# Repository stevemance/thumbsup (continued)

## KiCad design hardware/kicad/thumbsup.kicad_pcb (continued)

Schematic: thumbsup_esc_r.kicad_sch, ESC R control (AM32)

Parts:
C300: 4.7u; C_0603_1608Metric; LCSC C19666
C301, C302, C304, C305, C306, C308: 100n; C_0402_1005Metric; LCSC C1525
C303: 1u; C_0402_1005Metric; LCSC C52923
C307: 10n; C_0402_1005Metric; LCSC C15195
C309: 10u 25V; C_0805_2012Metric; LCSC C15850
C310: 100n 50V; C_0603_1608Metric; LCSC C14663
J30: SWD; SWD_1x05_P1.27mm_Pads
R300, R303, R305, R306, R307, R311, R312, R313: 10k; R_0402_1005Metric; LCSC C25744
R301: 10k DNP; R_0402_1005Metric; LCSC C25744; not fitted
R302: 100k; R_0402_1005Metric; LCSC C25741
R304: 1k; R_0402_1005Metric; LCSC C11702
R308, R309, R310: 3.3k; R_0402_1005Metric; LCSC C25890
U30: AT32F421K8U7; QFN-32-1EP_5x5mm_P0.5mm_EP3.3x3.3mm; LCSC C2965611
U31: HX6288 / FD6288Q; QFN-24-1EP_4x4mm_P0.5mm_EP2.7x2.7mm; LCSC C54423134
U32: INA180A1; SOT-23-5; LCSC C122228

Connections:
+3V3_MCU: C300.1, C301.1, C302.1, C303.1, C304.1, C308.1, J30.1, U30.1 (VDD), U30.5 (VDDA), U30.17 (VDD2), U32.5 (V+); also elsewhere on the board
+VDRV: C309.1, C310.1, U31.4 (VCC); also elsewhere on the board
/ESC R control (AM32)/R_BEMF_A: R305.2, R308.1, R311.1, U30.6 (PA0_BEMFA)
/ESC R control (AM32)/R_BEMF_B: R306.2, R309.1, R312.1, U30.10 (PA4_BEMFB)
/ESC R control (AM32)/R_BEMF_C: R307.2, R310.1, R313.1, U30.11 (PA5_BEMFC)
/ESC R control (AM32)/R_HIN1: U30.20 (PA10_AH), U31.22 (HIN1)
/ESC R control (AM32)/R_HIN2: U30.19 (PA9_BH), U31.23 (HIN2)
/ESC R control (AM32)/R_HIN3: U30.18 (PA8_CH), U31.24 (HIN3)
/ESC R control (AM32)/R_ISENSE: C307.1, R304.2, U30.9 (PA3_I)
/ESC R control (AM32)/R_LIN1: U30.15 (PB1_AL), U31.1 (LIN1)
/ESC R control (AM32)/R_LIN2: U30.14 (PB0_BL), U31.2 (LIN2)
/ESC R control (AM32)/R_LIN3: U30.13 (PA7_CL), U31.3 (LIN3)
/ESC R control (AM32)/R_NRST: C305.1, J30.4, U30.4 (NRST)
/ESC R control (AM32)/R_SWCLK: J30.3, U30.24 (PA14_SWCLK)
/ESC R control (AM32)/R_SWDIO: J30.2, U30.23 (PA13_SWDIO)
/ESC R control (AM32)/R_VN: R311.2, R312.2, R313.2, U30.7 (PA1_VN)
/ESC R control (AM32)/R_VSENSE: C306.1, R302.2, R303.1, U30.12 (PA6_V)
DSHOT_R: R301.1, U30.27 (PB4_DSHOT); also elsewhere on the board
GND: C300.2, C301.2, C302.2, C303.2, C304.2, C305.2, C306.2, C307.2, C308.2, C309.2, C310.2, J30.5, R300.2, R301.2, R303.2, R308.2, R309.2, R310.2, U30.33 (EP_VSS), U31.6 (COM), U31.25 (EP), U32.2 (GND); also elsewhere on the board
I_R_S+: U32.3 (+); also elsewhere on the board
I_R_S-: U32.4 (-); also elsewhere on the board
MOTOR_R_A: R305.1, U31.18 (VS1); also elsewhere on the board
MOTOR_R_B: R306.1, U31.15 (VS2); also elsewhere on the board
MOTOR_R_C: R307.1, U31.12 (VS3); also elsewhere on the board
unnamed: R304.1, U32.1
unnamed: R300.1, U30.31 (BOOT0)
R_HO1: U31.19 (HO1); also elsewhere on the board
R_HO2: U31.16 (HO2); also elsewhere on the board
R_HO3: U31.13 (HO3); also elsewhere on the board
R_LO1: U31.11 (LO1); also elsewhere on the board
R_LO2: U31.10 (LO2); also elsewhere on the board
R_LO3: U31.9 (LO3); also elsewhere on the board
R_VB1: U31.20 (VB1); also elsewhere on the board
R_VB2: U31.17 (VB2); also elsewhere on the board
R_VB3: U31.14 (VB3); also elsewhere on the board
VBAT: R302.1; also elsewhere on the board

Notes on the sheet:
ESC R: AM32 cell — AT32F421 (target AT32DEV_F421) + FD6288Q gate driver + sense networks. Power stage on sheet esc_r_bridge.
Stock-hex scaling: voltage divider 100k/10k (TARGET_VOLTAGE_DIVIDER 110), current 1 mΩ × INA180A1 (20 V/V) = 20 mV/A (MILLIVOLT_PER_AMP 20).
HO/LO/VS/VB → bridge sheet
SWD (first bootloader flash)
1: +3V3 2: SWDIO 3: SWCLK 4: NRST 5: GND
DShot pull-down — DNP (AT32 idles high for AM32 1-wire)
Pack voltage → PA6 (11:1)
Cell current: 1 mΩ shunt → INA180A1 (20 V/V) → RC → PA3
BEMF dividers 10k/3.3k (4:1) and 10k virtual-neutral star → comparator
Decoupling — at U pins (C300…: AT32 VDD/VDDA, INA180, FD6288 VCC)

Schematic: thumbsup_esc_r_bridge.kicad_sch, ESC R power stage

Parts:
C320, C321, C322: 100n 50V; C_0603_1608Metric; LCSC C14663
C323, C324: 10u 50V; C_1206_3216Metric; LCSC C13585
C325: 470u 25V hybrid; CP_Elec_10x10.5; LCSC C242138
D30, D31, D32: 1N5819WS; D_SOD-323; LCSC C191023
J31: MOTOR R; MotorHoles_1x03_P5.90mm
NT30, NT31: Kelvin; NetTie-2_Kelvin_0.4mm
Q30, Q31, Q32, Q33, Q34, Q35: HYG015N04LS1C2; PQFN-8-EP_6x5mm_P1.27mm_Generic; LCSC C2874970
R320, R321, R322, R323, R324, R325: 10; R_0402_1005Metric; LCSC C25077
R326, R327, R328, R329, R330, R331: 10k; R_0402_1005Metric; LCSC C25744
R332, R333, R334: 2.2; R_0603_1608Metric; LCSC C22939
R335: 1mΩ 3W; R_2512_Shunt_Kelvin; LCSC C46961745

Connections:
+VDRV: R332.1, R333.1, R334.1; also elsewhere on the board
/ESC R power stage/I_R+: NT30.1, Q31.1 (S), Q31.2 (S), Q31.3 (S), Q33.1 (S), Q33.2 (S), Q33.3 (S), Q35.1 (S), Q35.2 (S), Q35.3 (S), R327.2, R329.2, R331.2, R335.1
GND: C323.2, C324.2, C325.2, NT31.1, R335.2; also elsewhere on the board
I_R_S+: NT30.2; also elsewhere on the board
I_R_S-: NT31.2; also elsewhere on the board
MOTOR_R_A: C320.2, J31.1, Q30.1 (S), Q30.2 (S), Q30.3 (S), Q31.5 (D), R326.2; also elsewhere on the board
MOTOR_R_B: C321.2, J31.2, Q32.1 (S), Q32.2 (S), Q32.3 (S), Q33.5 (D), R328.2; also elsewhere on the board
MOTOR_R_C: C322.2, J31.3, Q34.1 (S), Q34.2 (S), Q34.3 (S), Q35.5 (D), R330.2; also elsewhere on the board
unnamed: D30.2 (A), R332.2
unnamed: D31.2 (A), R333.2
unnamed: D32.2 (A), R334.2
unnamed: Q30.4 (G), R320.2, R326.1
unnamed: Q31.4 (G), R321.2, R327.1
unnamed: Q32.4 (G), R322.2, R328.1
unnamed: Q33.4 (G), R323.2, R329.1
unnamed: Q34.4 (G), R324.2, R330.1
unnamed: Q35.4 (G), R325.2, R331.1
R_HO1: R320.1; also elsewhere on the board
R_HO2: R322.1; also elsewhere on the board
R_HO3: R324.1; also elsewhere on the board
R_LO1: R321.1; also elsewhere on the board
R_LO2: R323.1; also elsewhere on the board
R_LO3: R325.1; also elsewhere on the board
R_VB1: C320.1, D30.1 (K); also elsewhere on the board
R_VB2: C321.1, D31.1 (K); also elsewhere on the board
R_VB3: C322.1, D32.1 (K); also elsewhere on the board
VBAT: C323.1, C324.1, C325.1, Q30.5 (D), Q32.5 (D), Q34.5 (D); also elsewhere on the board

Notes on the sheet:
ESC R power stage: 3× half-bridge HYG015N04LS1C2 (40 V, 2 mΩ), bootstrap 2.2 Ω + 1N5819WS + 100 nF, low-side 1 mΩ shunt
Gate drive from +VDRV (9–12.6 V). Bulk: 2× 10 µF MLCC at the drains + 470 µF hybrid polymer (×2 on the weapon). Motor pads A/B/C on J (2 mm holes + top lands).
Kelvin: NT net-ties on the shunt pads; INA180 (this cell) + INA226 (log) sense from them
Bulk at the FET drains (VBAT): 2x 10 uF MLCC + hybrid polymer
Motor R pads

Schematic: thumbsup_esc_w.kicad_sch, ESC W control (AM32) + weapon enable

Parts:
C400: 4.7u; C_0603_1608Metric; LCSC C19666
C401, C402, C404, C405, C406, C408: 100n; C_0402_1005Metric; LCSC C1525
C403: 1u; C_0402_1005Metric; LCSC C52923
C407: 10n; C_0402_1005Metric; LCSC C15195
C409: 10u 25V; C_0805_2012Metric; LCSC C15850
C410: 100n 50V; C_0603_1608Metric; LCSC C14663
J40: SWD; SWD_1x05_P1.27mm_Pads
Q46: AP40P05; SOT-23; LCSC C2886385
Q47, Q48, Q49, Q50: AO3400A; SOT-23; LCSC C20917
R400, R403, R405, R406, R407, R411, R412, R413, R441: 10k; R_0402_1005Metric; LCSC C25744
R401: 10k DNP; R_0402_1005Metric; LCSC C25744; not fitted
R402, R442, R443: 100k; R_0402_1005Metric; LCSC C25741
R404: 1k; R_0402_1005Metric; LCSC C11702
R408, R409, R410: 3.3k; R_0402_1005Metric; LCSC C25890
R440: 4.7k; R_0603_1608Metric; LCSC C23162
R444: 47k; R_0402_1005Metric; LCSC C25792
TP40: WEAPON_EN; TestPoint_Pad_D1.5mm
U40: AT32F421K8U7; QFN-32-1EP_5x5mm_P0.5mm_EP3.3x3.3mm; LCSC C2965611
U41: HX6288 / FD6288Q; QFN-24-1EP_4x4mm_P0.5mm_EP2.7x2.7mm; LCSC C54423134
U42: INA180A1; SOT-23-5; LCSC C122228

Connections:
+3V3_MCU: C400.1, C401.1, C402.1, C403.1, C404.1, C408.1, J40.1, U40.1 (VDD), U40.5 (VDDA), U40.17 (VDD2), U42.5 (V+); also elsewhere on the board
+VDRV: Q46.2 (S), R440.1; also elsewhere on the board
/ESC W control (AM32) + weapon enable/W_BEMF_A: R405.2, R408.1, R411.1, U40.6 (PA0_BEMFA)
/ESC W control (AM32) + weapon enable/W_BEMF_B: R406.2, R409.1, R412.1, U40.10 (PA4_BEMFB)
/ESC W control (AM32) + weapon enable/W_BEMF_C: R407.2, R410.1, R413.1, U40.11 (PA5_BEMFC)
/ESC W control (AM32) + weapon enable/W_HIN1: U40.20 (PA10_AH), U41.22 (HIN1)
/ESC W control (AM32) + weapon enable/W_HIN2: U40.19 (PA9_BH), U41.23 (HIN2)
/ESC W control (AM32) + weapon enable/W_HIN3: U40.18 (PA8_CH), U41.24 (HIN3)
/ESC W control (AM32) + weapon enable/W_ISENSE: C407.1, R404.2, U40.9 (PA3_I)
/ESC W control (AM32) + weapon enable/W_LIN1: U40.15 (PB1_AL), U41.1 (LIN1)
/ESC W control (AM32) + weapon enable/W_LIN2: U40.14 (PB0_BL), U41.2 (LIN2)
/ESC W control (AM32) + weapon enable/W_LIN3: U40.13 (PA7_CL), U41.3 (LIN3)
/ESC W control (AM32) + weapon enable/W_NRST: C405.1, J40.4, Q49.3 (D), Q50.3 (D), U40.4 (NRST)
/ESC W control (AM32) + weapon enable/W_SWCLK: J40.3, U40.24 (PA14_SWCLK)
/ESC W control (AM32) + weapon enable/W_SWDIO: J40.2, U40.23 (PA13_SWDIO)
/ESC W control (AM32) + weapon enable/W_VN: R411.2, R412.2, R413.2, U40.7 (PA1_VN)
/ESC W control (AM32) + weapon enable/W_VSENSE: C406.1, R402.2, R403.1, U40.12 (PA6_V)
ARM_N: Q48.1 (G), Q50.1 (G); also elsewhere on the board
DSHOT_W: R401.1, U40.27 (PB4_DSHOT); also elsewhere on the board
GND: C400.2, C401.2, C402.2, C403.2, C404.2, C405.2, C406.2, C407.2, C408.2, C409.2, C410.2, J40.5, Q47.2 (S), Q48.2 (S), Q49.2 (S), Q50.2 (S), R400.2, R401.2, R403.2, R408.2, R409.2, R410.2, R442.2, R444.2, U40.33 (EP_VSS), U41.6 (COM), U41.25 (EP), U42.2 (GND); also elsewhere on the board
I_W_S+: U42.3 (+); also elsewhere on the board
I_W_S-: U42.4 (-); also elsewhere on the board
MOTOR_W_A: R405.1, U41.18 (VS1); also elsewhere on the board
MOTOR_W_B: R406.1, U41.15 (VS2); also elsewhere on the board
MOTOR_W_C: R407.1, U41.12 (VS3); also elsewhere on the board
unnamed: Q46.1 (G), Q47.3 (D), R440.2, R443.1
unnamed: Q47.1 (G), Q48.3 (D), R441.2, R442.1
unnamed: Q49.1 (G), R443.2, R444.1
unnamed: R404.1, U42.1
unnamed: R400.1, U40.31 (BOOT0)
VBAT: R402.1; also elsewhere on the board
WEAPON_EN: R441.1, TP40.1; also elsewhere on the board
W_HO1: U41.19 (HO1); also elsewhere on the board
W_HO2: U41.16 (HO2); also elsewhere on the board
W_HO3: U41.13 (HO3); also elsewhere on the board
W_LO1: U41.11 (LO1); also elsewhere on the board
W_LO2: U41.10 (LO2); also elsewhere on the board
W_LO3: U41.9 (LO3); also elsewhere on the board
W_VB1: U41.20 (VB1); also elsewhere on the board
W_VB2: U41.17 (VB2); also elsewhere on the board
W_VB3: U41.14 (VB3); also elsewhere on the board
W_VCC: C409.1, C410.1, Q46.3 (D), U41.4 (VCC); also elsewhere on the board

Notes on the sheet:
ESC W: AM32 cell — AT32F421 (target AT32DEV_F421) + FD6288Q gate driver + sense networks. Power stage on sheet esc_w_bridge.
Stock-hex scaling: voltage divider 100k/10k (TARGET_VOLTAGE_DIVIDER 110), current 1 mΩ × INA180A1 (20 V/V) = 20 mV/A (MILLIVOLT_PER_AMP 20).
HO/LO/VS/VB → bridge sheet
SWD (first bootloader flash)
1: +3V3 2: SWDIO 3: SWCLK 4: NRST 5: GND
DShot pull-down — DNP (AT32 idles high for AM32 1-wire)
Pack voltage → PA6 (11:1)
Cell current: 1 mΩ shunt → INA180A1 (20 V/V) → RC → PA3
BEMF dividers 10k/3.3k (4:1) and 10k virtual-neutral star → comparator
Decoupling — at U pins (C400…: AT32 VDD/VDDA, INA180, FD6288 VCC)
Weapon hardware enable: W_VCC = +VDRV only when WEAPON_EN (GP9) AND ARM link closed. Q49 (from the gate node) and Q50 (from ARM_N) hold the AT32 in reset while disabled,
so no 3.3 V is ever driven into an unpowered FD6288 (abs max VIN <= VCC+0.3 V). R440 4.7k keeps Vsg(Q46) < 0.45 V when off (SPICE); R442 keeps the weapon off if the Pico pin floats.

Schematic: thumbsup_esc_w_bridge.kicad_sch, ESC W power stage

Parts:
C420, C421, C422: 100n 50V; C_0603_1608Metric; LCSC C14663
C423, C424: 10u 50V; C_1206_3216Metric; LCSC C13585
C425: 470u 25V polymer 4A; CP_Elec_10x12.5; LCSC C46528073
D40, D41, D42: 1N5819WS; D_SOD-323; LCSC C191023
J41: MOTOR W; MotorHoles_1x03_P5.90mm
NT40, NT41: Kelvin; NetTie-2_Kelvin_0.4mm
Q40, Q41, Q42, Q43, Q44, Q45: HYG015N04LS1C2; PQFN-8-EP_6x5mm_P1.27mm_Generic; LCSC C2874970
R420, R421, R422, R423, R424, R425: 10; R_0402_1005Metric; LCSC C25077
R426, R427, R428, R429, R430, R431: 10k; R_0402_1005Metric; LCSC C25744
R432, R433, R434: 2.2; R_0603_1608Metric; LCSC C22939
R435: 1mΩ 3W; R_2512_Shunt_Kelvin; LCSC C46961745

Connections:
/ESC W power stage/I_W+: NT40.1, Q41.1 (S), Q41.2 (S), Q41.3 (S), Q43.1 (S), Q43.2 (S), Q43.3 (S), Q45.1 (S), Q45.2 (S), Q45.3 (S), R427.2, R429.2, R431.2, R435.1
GND: C423.2, C424.2, C425.2, NT41.1, R435.2; also elsewhere on the board
I_W_S+: NT40.2; also elsewhere on the board
I_W_S-: NT41.2; also elsewhere on the board
MOTOR_W_A: C420.2, J41.1, Q40.1 (S), Q40.2 (S), Q40.3 (S), Q41.5 (D), R426.2; also elsewhere on the board
MOTOR_W_B: C421.2, J41.2, Q42.1 (S), Q42.2 (S), Q42.3 (S), Q43.5 (D), R428.2; also elsewhere on the board
MOTOR_W_C: C422.2, J41.3, Q44.1 (S), Q44.2 (S), Q44.3 (S), Q45.5 (D), R430.2; also elsewhere on the board
unnamed: D40.2 (A), R432.2
unnamed: D41.2 (A), R433.2
unnamed: D42.2 (A), R434.2
unnamed: Q40.4 (G), R420.2, R426.1
unnamed: Q41.4 (G), R421.2, R427.1
unnamed: Q42.4 (G), R422.2, R428.1
unnamed: Q43.4 (G), R423.2, R429.1
unnamed: Q44.4 (G), R424.2, R430.1
unnamed: Q45.4 (G), R425.2, R431.1
VBAT: C423.1, C424.1, C425.1, Q40.5 (D), Q42.5 (D), Q44.5 (D); also elsewhere on the board
W_HO1: R420.1; also elsewhere on the board
W_HO2: R422.1; also elsewhere on the board
W_HO3: R424.1; also elsewhere on the board
W_LO1: R421.1; also elsewhere on the board
W_LO2: R423.1; also elsewhere on the board
W_LO3: R425.1; also elsewhere on the board
W_VB1: C420.1, D40.1 (K); also elsewhere on the board
W_VB2: C421.1, D41.1 (K); also elsewhere on the board
W_VB3: C422.1, D42.1 (K); also elsewhere on the board
W_VCC: R432.1, R433.1, R434.1; also elsewhere on the board

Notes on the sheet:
ESC W power stage: 3× half-bridge HYG015N04LS1C2 (40 V, 2 mΩ), bootstrap 2.2 Ω + 1N5819WS + 100 nF, low-side 1 mΩ shunt
Gate drive from W_VCC (9–12.6 V). Bulk: 2× 10 µF MLCC at the drains + 470 µF hybrid polymer (×2 on the weapon). Motor pads A/B/C on J (2 mm holes + top lands).
Kelvin: NT net-ties on the shunt pads; INA180 (this cell) + INA226 (log) sense from them
Bulk at the FET drains (VBAT): 2x 10 uF MLCC + hybrid polymer
Motor W pads

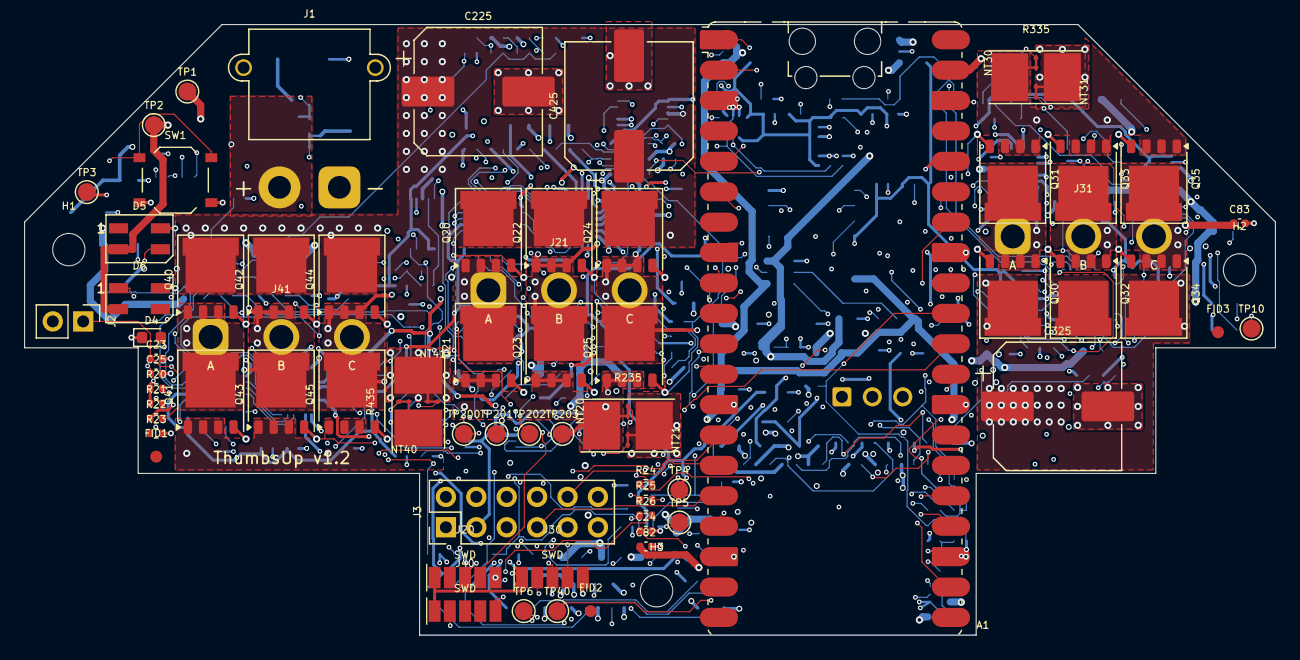
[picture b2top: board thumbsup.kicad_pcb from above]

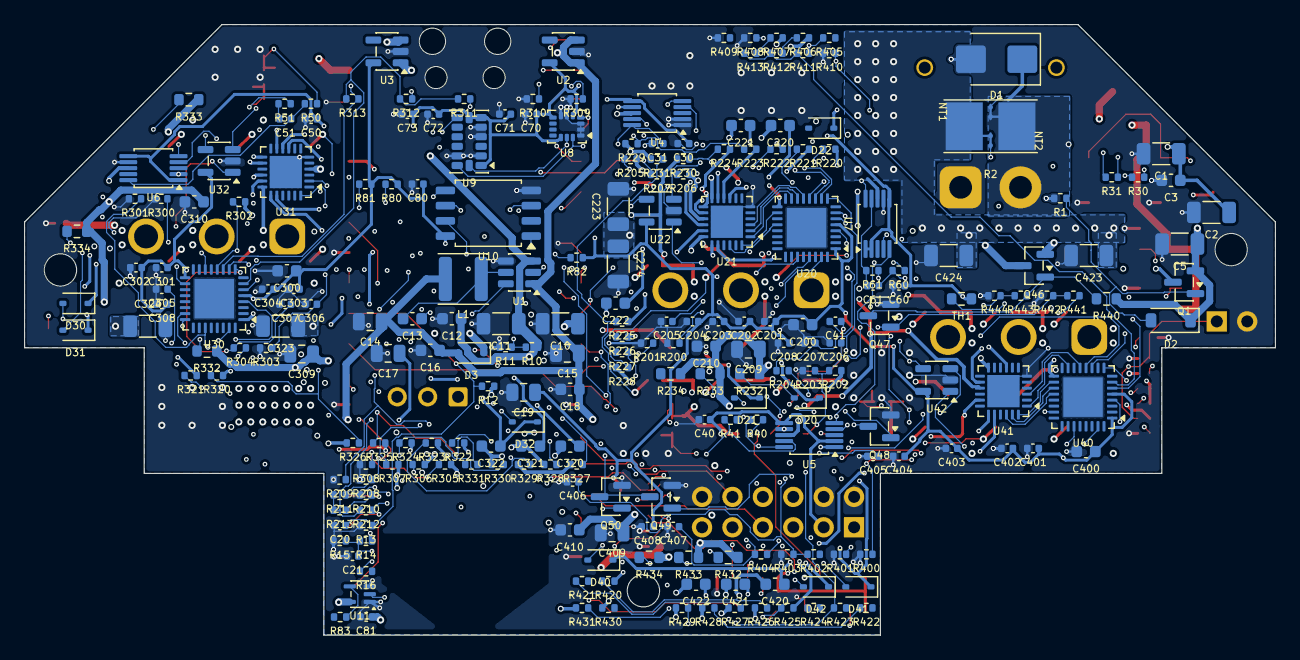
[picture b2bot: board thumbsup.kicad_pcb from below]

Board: 4 copper layers, 104.5 x 51.0 mm, 307 parts (233 on the bottom side), 182 nets.

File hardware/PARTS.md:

# ThumbsUp v1 parts (rev v1.2, 2026-09-04)

Every LCSC number below was read from its lcsc.com / jlcpcb.com product page on
2026-09-03; "Basic" / "Extended" is JLCPCB's class on that page.  The BOM field `LCSC`
on every symbol in `kicad/` carries the same number (source: `tools/sch/circuit.py`).
Design rationale and review history: [REVIEW.md](REVIEW.md); layout constraints:
[LAYOUT.md](LAYOUT.md).

**Before ordering:** confirm JLC stock the same day for the low-stock lines marked ⚠;
FD6288Q (C328453) is out of stock, so the driver is ordered as **HX6288 C54423134**
(pin-identical per its datasheet, EP = COM). Confirm XT30 polarity against a physical
connector (the Amass drawing has no "+" mark; the KiCad footprint puts "+" on pad 2).

Assembly: JLC Standard PCBA, both sides (FETs, shunts, cans, TPs, LEDs on top; ICs and
passives on the bottom). Hand-soldered after SMT: Pico W (castellated), J1 XT30, J2/J3
headers, the nine motor leads. Hybrid polymer cans are SMT. SWD is a 1×5 pad row
(`thumbsup:SWD_1x05_P1.27mm_Pads`) for pogo pins or wires.

## ICs and semiconductors

| Qty | Ref | Part | LCSC | Class | Notes |
|---|---|---|---|---|---|
| 1 | A1 | Raspberry Pi Pico W | — | — | `Module:RaspberryPi_Pico_W_SMD_HandSolder`; custom symbol `thumbsup:PicoW` (grounds typed power-in) |
| 3 | U20 U30 U40 | Artery AT32F421K8U7, QFN-32 5×5 | C2965611 | Ext | AM32 `AT32DEV_F421`; EP = VSS (only ground) |
| 3 | U21 U31 U41 | ZHHXDZ **HX6288**, QFN-24 4×4 (FD6288Q C328453 alternate) | C54423134 | Ext | pin-identical to FD6288Q; EP (pin 25) = COM; 2 085 in stock |
| 3 | U22 U32 U42 | TI INA180A1IDBVR, SOT-23-5 | C122228 | Ext | 20 V/V, ±150 µV; 15 100 in stock |
| 18 | Q20–25 Q30–35 Q40–45 | Huayi HYG015N04LS1C2, PDFN 5×6 | C2874970 | Ext | 40 V, 2.0 mΩ @ 4.5 V; **leads 1–3 = S, 4 = G, tab = D** (custom symbol) |
| 4 | U4–U7 | TI INA226AIDGSR, VSSOP-10 | C49851 | Ext | 0x40 / 0x41 / 0x44 / 0x45 |
| 1 | U1 | Diodes AP63205WU-7, TSOT-23-6 | C2071056 | Ext | 5 V / 2 A buck, FB→VOUT, EN 100k/27k (on 5.4 V / off 4.6 V) |
| 2 | U2 U3 | Diodes AP2112K-3.3TRG1, SOT-23-5 | C51118 | Ext | +3V3_A (sensors) / +3V3_MCU (AT32 ×3, flash) |
| 1 | U10 | Winbond W25Q128JVSIQ, SOIC-8 208 mil | C97521 | **Basic** | 16 MB match log |
| 1 | U8 | ST LSM6DS3TR-C, LGA-14 | C967633 | Ext | 0x6A (SA0 = GND, CS = VDDIO, SDx/SCx = GND) |
| 1 | U9 | ADI ADXL375BCCZ, LGA-14 | C579466 | Ext ⚠ | 0x53; 179 in stock, $22 |
| 1 | U11 | 74AHCT1G125GW, SOT-353 | C52953352 | Ext ⚠ | SK6812 level shift; 470 in stock |
| 2 | Q1 Q46 | AllPower AP40P05 P-MOSFET, SOT-23 | C2886385 | Ext | G=1 S=2 D=3 (DS V1.1), Vgs ±20 V, 65–120 mΩ, 5 A: logic RPP / weapon VCC switch |
| 4 | Q47–Q50 | AOS AO3400A, SOT-23 | C20917 | **Basic** | weapon enable AND, reset hold ×2 |
| 1 | D1 | Yangjie SMBJ15A, SMB | C699013 | Ext | TVS 15 V standoff; **3S only** |
| 1 | D2 | MMSZ5242B 12 V, SOD-123 | C21567 | Ext | RPP gate clamp |
| 10 | D3 D20–22 D30–32 D40–42 | 1N5819WS, SOD-323 | C191023 | **Basic** | VSYS isolation + 9 bootstrap |
| 1 | D4 | KENTO KT-0603R red LED | C2286 | **Basic** | pack-present LED (from +VDRV) |
| 2 | D5 D6 | OPSCO SK6812MINI-C | C7423117 | Ext | custom footprint `thumbsup:LED_SK6812MINI-C` from the DS land pattern |
| 1 | L1 | cjiang FHD4020S-4R7MT 4.7 µH | C602031 | Ext | Isat 4.9 A, 4×4×2 mm (footprint `L_Changjiang_FNR4020S`, check pads) |
| 1 | TH1 | Murata NCP18XH103F03RB 10 k NTC 0603 | C13564 | Ext | B = 3380 K, at the weapon FETs |
| 1 | SW1 | XKB TS-1187A-B-A-B tactile 5.1×5.1 | C318884 | **Basic** | footprint `SW_Push_1P1T_XKB_TS-1187A` |
| 1 | J1 | Amass XT30PW-M30.G.Y | C431092 | Ext | pack input through a back-wall slot; it is also the SPARC disconnect (J4 dropped in v1.2); "+" = pad 2 |
| 4 | R2 R235 R335 R435 | JIERR RE2512F3R001 1 mΩ 3 W 2512 | C46961745 | Ext | footprint `thumbsup:R_2512_Shunt_Kelvin`; Kelvin via NT net-ties |
| 8 | NT1 NT2 NT20 NT21 NT30 NT31 NT40 NT41 | `thumbsup:NetTie-2_Kelvin_0.4mm` | — | — | copper-only pads in the shunt pad gap; no BOM line |
| 2 | C225 C325 | Panasonic **EEHZK1E471P** 470 µF 25 V hybrid polymer, SMD 10×10.2 | C242138 | Ext | 20 mΩ; footprint `CP_Elec_10x10.5` |
| 1 | C425 | KNSCHA 118EC421 470 µF 25 V hybrid polymer, SMD 10×12.5 | C46528073 | Ext | 14 mΩ / 4 A ripple for the weapon; footprint `CP_Elec_10x12.5`; C4 (entry) and C426 dropped in v1.2 — all three cans sit on the one VBAT pour |

## Passives (0402 1 % / 0402 X7R unless noted; all Basic unless marked)

| Qty | Value | LCSC | Where |
|---|---|---|---|
| 32 | 10 Ω | C25077 | INA226 filters ×8, FET gate R ×18, R?4 not used — see 1 k |
| 9 | 2.2 Ω 0603 | C22939 | bootstrap R?32–34 |
| 3 | 100 Ω | C25076 | DShot series R24–R26 |
| 1 | 330 Ω | C25104 | SK6812 series |
| 4 | 1 kΩ | C11702 | power LED (from +VDRV, ~10 mA), ISENSE RC ×3 |
| 2 | 2.2 kΩ | C25879 | I2C pull-ups |
| 10 | 3.3 kΩ | C25890 | BEMF bottom ×9, NTC divider R23 |
| 1 | 4.7 kΩ 0603 | C23162 | R440 weapon VCC gate pull-up (stiff) |
| 52 | 10 kΩ | C25744 | pull-ups/downs, BEMF top, VN star, Rgs, dividers, R201/301/401 **DNP** |
| 1 | 22 kΩ | C25768 | pack divider low |
| 1 | 27 kΩ | C25771 (Ext) | buck EN divider low |
| 1 | 47 kΩ | C25792 | reset-hold divider |
| 9 | 100 kΩ | C25741 | RPP gate, EN divider, pack divider, AT32 V-div ×3, weapon enable ×3 |
| 38 | 100 nF 16 V 0402 | C1525 | logic decoupling, RC filters, RUN (logic rails only) |
| 15 | 100 nF 50 V 0603 X7R | C14663 | +VDRV / bootstrap ×9 / driver VCC |
| 3 | 10 nF 0402 | C15195 | ISENSE RC |
| 4 | 1 µF 25 V 0402 | C52923 | ADXL VS, AT32 VDDA ×3 |
| 2 | 1 µF 50 V 0603 (X5R) | C15849 | LDO inputs C16/C18 |
| 3 | 4.7 µF 16 V 0603 | C19666 | AT32 VDD bulk |
| 5 | 10 µF 25 V 0805 (X5R) | C15850 | LDO outputs ×2, driver VCC ×3 |
| 2 | 22 µF 25 V 0805 | C45783 | buck out |
| 11 | 10 µF 50 V 1206 (X5R, 85 °C) | C13585 | pack entry ×2, +VDRV, buck in ×2, FET drains ×6 (bottom side under the high-FET tabs, via into the VBAT pour); X7R alt C89632 (Ext) |
| 1 | 1×2 header | — | J2 ARM link |
| 1 | 2×6 header | — | J3 expansion |
| 3 | 1×5 header (or pogo pads) | — | SWD |
| 3 | motor lead holes | — | `thumbsup:MotorHoles_1x03_P5.90mm`: 3 × 2.0 mm plated holes between the FET rows |
| 12 | test point 1.5 mm | — | TP1–TP6 rails, TP10 DSHOT_L, TP200–203 L cell (ISENSE, VSENSE, TLM, I_L+), TP40 WEAPON_EN |
| 3 + 3 | M2.5 holes, fiducials | — | H1–H3 (`MountingHole_2.7mm_M2.5`), FID1–FID3 |

## Scaling that the stock AM32 hex expects

* `TARGET_VOLTAGE_DIVIDER 110` → 100 kΩ / 10 kΩ on PA6 (12.6 V → 1.15 V).
* `MILLIVOLT_PER_AMP 20`, `CURRENT_OFFSET 0` → 1 mΩ × INA180A1 (20 V/V) = 20 mV/A on PA3 (bus-side average current; regen reads 0).
* BEMF 10 k / 3.3 k, virtual neutral 3 × 10 k into PA1 (comparator INP).

## Dropped since v1.0

Through-hole electrolytics (C43839 / C503217: wrong footprint class, ~0.6 A ripple), 10 Ω
bootstrap resistors (2 V of drive lost at 48 kHz), 2.54 mm pin headers as motor pads, Omron
B3U footprint for the XKB switch, `Q_NMOS_GSD` for the PDFN FETs, the `C1361247?` INA180
placeholder, R440 100 k (weapon FET never turned off).

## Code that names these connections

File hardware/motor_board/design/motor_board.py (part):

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two("R11", "100R 0603", "Resistor_SMD:R_0603_1608Metric", "BAL4", "BMS_BAT", LCSC["R100R_0603"],
    "U8 BAT/REGSRC supply from the balance lead top (TI 8.2: >= 50 ohm filter); 0603 for the ~0.7 mJ plug-in pulse into C9")
two("C9", "4.7uF 50V X7R", C1206, "BMS_BAT", "GND", LCSC["4u7_50V_1206"], "U8 BAT decoupling: >= 1 uF effective at 16.8 V (TI min 1 uF); 50 V also fits 6S")
two("C117", "100nF 50V", C0603, "BMS_BAT", "GND", LCSC["100n_50V_0603"], "U8 BAT / REGSRC local HF bypass at pins 16/17 (C9, the 4.7 uF bulk, sits ~19 mm away on the board)")
two("C11", "4.7uF 16V", C0603, "BMS_REG", "GND", LCSC["4u7_16V_0603"], "U8 REGOUT (enabled by OTP default, TI min 1 uF effective at 3.3 V)")

# power LED (SPARC: visible power indicator independent of firmware)
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    two(f"R{k}", "68k 1%", R0402, f"W_{ph}", f"W_V{ph}", LCSC["R68k"], f"phase {ph} divider top (25.2 V -> 3.23 V)")
    two(f"R{k+1}", "10k 1%", R0402, f"W_V{ph}", "GND", LCSC["R10k"], f"phase {ph} divider bottom")
    two(f"C{41 + ord(ph) - 65}", "1nF 50V", C0402, f"W_V{ph}", "GND", LCSC["1n_50V_0402"],
        f"phase {ph} divider filter at the MCU (8.8 us; ADC sample kickback, ring suppression, keeps a TVS-level spike below the 4 V abs max of PA5/PC3 (TT_a); PC4 is FT_fa)")

# weapon interlock: each phase enable INLx = TIM1_CHxN AND W_ARM_S (dynamic ARM from the compute board, below).  In 3x PWM mode
# INLx = 0 puts the phase Hi-Z whatever INHx does, so without ARM the weapon coasts and cannot be driven, and the
# DRV8323 stays awake (ENABLE = W_EN from the MCU) so nFAULT/CSA keep working.  W_ARM_S also goes to the MCU (PC15).
part("U6", "SN74LVC08ABQAR", "Package_DFN_QFN:DHWQFN-14-1EP_2.5x3mm_P0.5mm_EP1x1.5mm",
     {"1": ("1A", "W_INLA_M"), "2": ("1B", "W_ARM_S"), "3": ("1Y", "W_INLA"),
      "4": ("2A", "W_INLB_M"), "5": ("2B", "W_ARM_S"), "6": ("2Y", "W_INLB"), "7": ("GND", "GND"),
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# dynamic ARM: the compute board must keep toggling W_ARM_CLK from its control loop (>= 500 Hz, 3.3 V square wave).
# C15/D9 rectify it into W_ARM (2.5-2.9 V at >= 500 Hz); stuck high, stuck low, a hung compute board or an unplugged header
# let R41 discharge C16 below the U14 Schmitt threshold in 30-200 ms, which floats the weapon (INLx = 0).  W_ARM_S
# (U14 output) feeds U6 and PC15.
two("R18", "100k", R0402, "W_ARM_CLK", "GND", LCSC["R100k"], "W_ARM_CLK defined low with the header unplugged")
two("C15", "470nF 25V", C0603, "W_ARM_CLK", "ARM_AC", LCSC["470n_25V_0603"], "ARM charge pump: coupling cap (a DC level passes nothing; < C16 so a clock stuck high cannot hold W_ARM up)")
part("D9", "BAT54S", "Package_TO_SOT_SMD:SOT-23",
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    "ARM bleed: W_ARM below U14's VT- 30-200 ms after the toggling stops (stuck high or low, 25-85 C incl. D9 leakage, VT- 0.8-1.33 V); swamps input leakage")
part("U14", "74LVC1G17SE-7", "Package_TO_SOT_SMD:SOT-353_SC-70-5",
     {"1": ("NC", "NC"), "2": ("A", "W_ARM"), "3": ("GND", "GND"), "4": ("Y", "W_ARM_S"), "5": ("VCC", "+3V3")}, LCSC["LVC1G17"],
     "Schmitt buffer on the slow RC ARM level (Diodes DS35124: SOT-353 1 NC, 2 A, 3 GND, 4 Y, 5 VCC; VT+ <= 2.0 V, VT- >= 0.8 V at 3 V): clean edges into U6 and PC15")
two("C17", "100nF 16V", C0402, "+3V3", "GND", LCSC["100n_16V_0402"], "U14 decoupling")
two("R19", "10k 1%", R0402, "W_ARM_S", "GND", LCSC["R10k"], "W_ARM_S held low if U14's output opens or U14 is unpowered (U6 inputs and PC15 must not float; 10 k beats 3 x 5 uA worst-case input leakage)")
for k, ph in enumerate("ABC"):
    two(f"R{47 + k}", "100k", R0402, f"W_INL{ph}_M", "GND", LCSC["R100k"], f"TIM1_CH{3 - k}N ({ph}: {['PB15', 'PA12', 'PA7'][k]}) low while the MCU is in reset (U6 input must not float)")
two("R42", "10k 1%", R0402, "W_nFAULT", "+3V3", LCSC["R10k"], "nFAULT pull-up")
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two("R43", "10k 1%", R0402, "+3V3", "W_NTC", LCSC["R10k"], "weapon FET NTC pull-up")
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# drive sensor connectors: Hall (UVW) or MT6701 (ABZ or UVW), motor NTC.
# VS: JP selects 3.3 V (default) or 5 V, then a 100 mA current-limited switch so a crushed cable cannot pull down
# the logic rails.  S1-S3: 4.7k pull-ups (open-drain Halls) into a 3.3 V Schmitt buffer whose inputs tolerate 5.5 V,
# so 5 V push-pull sensors are safe and the MCU's TT_a pins (PB0, PB10) never see more than 3.3 V.
for s, jref, jp, rt, ub, us, rp, cn, sr, dt in (("L", "J2", "JP1", "R52", "U9", "U11", 54, 45, 110, 7),
                                               ("R", "J3", "JP2", "R53", "U10", "U12", 57, 48, 114, 8)):
    part(jref, "SH1.0 6P SMD vertical", "Connector_JST:JST_SH_BM06B-SRSS-TB_1x06-1MP_P1.00mm_Vertical",
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MCU_PINS = {
    # pin: (name, net, required alternate function or '' for GPIO/analog-only)
    # co-assigned with the v2 placement (kicad/v2/pinsolve.py, 2026-09-29); U1 at (43.5, 26.25), rotated 180
    "1": ("VBAT", "+3V3", ""), "2": ("PC13", "NC", ""), "3": ("PC14", "W_EN", ""),
    "4": ("PC15", "W_ARM_S", ""), "5": ("PF0", "R_MTEMP", "ADC1_IN10"), "6": ("PF1", "L_MTEMP", "ADC2_IN10"),
    "7": ("PG10-NRST", "NRST", ""), "8": ("PC0", "W_INHC", "TIM1_CH1"), "9": ("PC1", "W_INHB", "TIM1_CH2"),
    "10": ("PC2", "R_INHB", "TIM20_CH2"), "11": ("PC3", "W_VC", "ADC1_IN9"), "12": ("PA0", "W_SOA", "COMP3_INP"),
    "13": ("PA1", "W_SOC", "COMP1_INP"), "14": ("PA2", "VBAT_SNS", "ADC1_IN3"), "15": ("VSS", "GND", ""),
    "16": ("VDD", "+3V3", ""), "17": ("PA3", "W_SOB", "COMP2_INP"), "18": ("PA4", "W_NTC", "ADC2_IN17"),
    "19": ("PA5", "W_VB", "ADC2_IN13"), "20": ("PA6", "W_nFAULT", "TIM1_BKIN"), "21": ("PA7", "W_INLC_M", "TIM1_CH1N"),
    "22": ("PC4", "W_VA", "ADC2_IN5"), "23": ("PC5", "INA_nCS", ""), "24": ("PB0", "R_S3", "TIM3_CH3"),
    "25": ("PB1", "R_SOA_F", "ADC3_IN1"), "26": ("PB2", "R_INHC", "TIM20_CH1"), "27": ("VSSA", "GND", ""),
    "28": ("VREF+", "+3V3A", ""), "29": ("VDDA", "+3V3A", ""), "30": ("PB10", "L_S3", "TIM2_CH3"),
    "31": ("VSS", "GND", ""), "32": ("VDD", "+3V3", ""), "33": ("PB11", "R_nCS", ""),
    "34": ("PB12", "R_SOB_F", "ADC4_IN3"), "35": ("PB13", "R_SOC_F", "ADC3_IN5"), "36": ("PB14", "L_SOA_F", "OPAMP5_VINP"),
    "37": ("PB15", "W_INLA_M", "TIM1_CH3N"), "38": ("PC6", "L_INHA", "TIM8_CH1"), "39": ("PC7", "L_INHB", "TIM8_CH2"),
    "40": ("PC8", "R_INHA", "TIM20_CH3"), "41": ("PC9", "R_nFAULT", ""), "42": ("PA8", "L_SOB_F", "ADC5_IN1"),
    "43": ("PA9", "L_SOC_F", "ADC5_IN2"), "44": ("PA10", "W_INHA", "TIM1_CH3"), "45": ("PA11", "DRV_OFF", ""),
    "46": ("PA12", "W_INLB_M", "TIM1_CH2N"), "47": ("VSS", "GND", ""), "48": ("VDD", "+3V3", ""),
    "49": ("PA13", "SWDIO", "SYS_JTMS-SWDIO"), "50": ("PA14", "SWCLK", "SYS_JTCK-SWCLK"), "51": ("PA15", "L_S1", "TIM2_CH1"),
    "52": ("PC10", "SPI_SCK", "SPI3_SCK"), "53": ("PC11", "SPI_MISO", "SPI3_MISO"), "54": ("PC12", "SPI_MOSI", "SPI3_MOSI"),
    "55": ("PD2", "L_nFAULT", "TIM8_BKIN"), "56": ("PB3", "L_S2", "TIM2_CH2"), "57": ("PB4", "R_S1", "TIM3_CH1"),
    "58": ("PB5", "R_S2", "TIM3_CH2"), "59": ("PB6", "MB_TX", "USART1_TX"), "60": ("PB7", "MB_RX", "USART1_RX"),
    "61": ("PB8-BOOT0", "L_nCS", ""), "62": ("PB9", "L_INHC", "TIM8_CH3"), "63": ("VSS", "GND", ""),
    "64": ("VDD", "+3V3", ""),
}
part("U1", "STM32G474RET6", "Package_QFP:LQFP-64_10x10mm_P0.5mm", {p: (n, net) for p, (n, net, _) in MCU_PINS.items()},
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two("C67", "100nF 16V", C0402, "NRST", "GND", LCSC["100n_16V_0402"], "NRST (internal pull-up)")
two("R63", "68k 1%", R0402, "VBAT", "VBAT_SNS", LCSC["R68k"], "pack divider top (25.2 V -> 3.23 V)")
two("R64", "10k 1%", R0402, "VBAT_SNS", "GND", LCSC["R10k"], "pack divider bottom")
two("R33", "100k", R0402, "VBAT_SNS", "VBAT_SNS_H", LCSC["R100k"], "header branch of the pack divider: a compute-board pin's reset pull-down (RP2040 ~50 k) shifts the MCU reading < 6 % instead of 10-15 %; the compute board reads it through this 100 k (add ~10 nF at its ADC pin)")
two("C68", "100nF 16V", C0402, "VBAT_SNS", "GND", LCSC["100n_16V_0402"], "pack divider filter (0.87 ms; the fast bus OV trip is the INA239 BOVL alert)")
two("C74", "100nF 16V", C0402, "+3V3", "GND", LCSC["100n_16V_0402"], "U1 VBAT pin 1")
two("C72", "100nF 16V", C0402, "L_MTEMP", "GND", LCSC["100n_16V_0402"], "motor L NTC filter at PF1")
two("C73", "100nF 16V", C0402, "R_MTEMP", "GND", LCSC["100n_16V_0402"], "motor R NTC filter for PF0, placed at the R117 (connector) end, not at the MCU pin")
# drive CSA outputs: TI SLVSH07 9.2.1.1.6 RC (330 ohm + 22 pF) at each ADC / OPAMP pin
for s in "LR":
    for ph in "ABC":
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
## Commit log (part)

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2025-09-16 Initial commit: Complete antweight robot control system
    Features:
    - Raspberry Pi Pico W based control system
    - Bluetooth gamepad support (PB Tails Crush/Xbox 360)
    - Differential drive with exponential curves
    - Variable speed weapon control with safety features
    - Integrated AM32 ESC programming via PWM line
2025-09-16 docs: Add contributing guidelines
2025-09-16 refactor: Update branding from Antweight to ThumbsUp
    - Updated all references in scripts and tools
    - Changed build artifact name to thumbsup-firmware
    - Maintained functionality while improving branding consistency
2025-09-16 fix: Update GitHub Actions to v4 to resolve deprecation warnings
    - Updated actions/checkout from v3 to v4
    - Updated actions/upload-artifact from v3 to v4
    - Resolves GitHub Actions deprecation notices
2025-09-16 refactor: Complete rebranding from antweight-robot to thumbsup
    - Updated all firmware binary names to thumbsup.uf2
    - Renamed KiCad project files
    - Updated all documentation references
    - Fixed all build scripts and tools
    - Ensures consistent naming throughout the project
2025-09-16 feat: Integrate Bluepad32 for Bluetooth gamepad support
    - Replace custom bluetooth implementation with Bluepad32
    - Add bluetooth_platform.c as Bluepad32 platform implementation
    - Update CMakeLists.txt to match pico_controller configuration
    - Use Bluepad32's BTstack with proper configuration
    - Successfully builds and generates UF2 file
    The firmware now uses Bluepad32 for gamepad support, providing
2025-09-16 docs: Update all documentation for Bluepad32 integration
    - Update README with Bluepad32 setup and universal controller support
    - Create comprehensive building.md with troubleshooting guide
    - Add bluepad32_integration.md for customization and debugging
    - Update CONTRIBUTING.md with new development workflow
    - Document supported controllers and pairing process
    - Add safety considerations and performance tips
2025-09-17 feat: Enhance safety systems for combat robot operation
    - Add comprehensive safety test suite that runs at startup
    - Implement continuous safety monitoring with violation counting
    - Add emergency stop hold time requirement (2 seconds) to prevent accidental resets
    - Improve integer overflow protection in all motor control calculations
    - Add battery voltage validation before weapon arming
    - Enhance failsafe timeout handling with increased reliability (1500ms)
2025-09-17 docs: Add comprehensive user manual and safety documentation
    - Create detailed USER_MANUAL.md with complete operating instructions
    - Add QUICK_REFERENCE.md for competition use
    - Document all 6 startup safety tests and their pass/fail criteria
    - Detail controller mappings and control functions
    - Add LED indicator reference guide
    - Include emergency procedures and troubleshooting
2025-09-17 feat: Add diagnostic mode with web dashboard (currently disabled)
    - Implement dual-mode system: Competition (Bluetooth) and Diagnostic (WiFi)
    - Create comprehensive web dashboard with real-time telemetry
    - Add virtual joystick control interface for drive testing
    - Implement weapon control with safety interlocks
    - Add event logging system with timestamps
    - Create JSON API for telemetry and control endpoints
2025-09-17 docs: Clarify diagnostic mode status and build requirements
    - Diagnostic mode is fully implemented but requires separate build
    - CYW43 arch must be chosen at compile time (WiFi OR Bluetooth)
    - Cannot link both stacks in same binary due to SDK limitations
    - Mode selection code is ready but needs two firmware variants
    The feature works perfectly when built separately. See DIAGNOSTIC_MODE.md
    for instructions on creating a diagnostic build variant.
2025-09-17 fix: Address all critical issues and implement improvements from code review
    Critical fixes:
    - Move CLAMP/MIN/MAX macros to config.h to fix compilation issues
    - Fix duplicate variable declaration in switch case by adding scope braces
    - Fix integer division precision loss in weapon ramping using float calculation
    - Add watchdog timer with 1-second timeout and periodic feeding
    - Replace all magic numbers with named constants
2025-09-17 docs: Add comprehensive hardware setup guide
    - Create detailed HARDWARE_SETUP.md with complete pinout diagram
    - Document safety button configuration and usage
    - Add voltage divider circuit for battery monitoring
    - Include LED indicator meanings and states
    - Document power requirements and wiring best practices
    - Add testing procedures and troubleshooting guide
2025-09-18 feat: Add interactive controller test mode with proper IMU calibration
    - Implemented test mode activated by holding L+R shoulder buttons for 1 second
    - Real-time display of all controller inputs using ANSI terminal control
    - Proper gyroscope scaling based on Nintendo Switch reverse engineering docs
    - Raw sensor values multiplied by 0.070 for deg/s conversion
    - Accounts for Bluepad32's 1000x scaling factor
    - Applied bias correction for zero drift when stationary
2025-11-18 fix: Configure for F2822-1100KV motor - CRITICAL current limit fix
    - CRITICAL: Reduce current limit from 40A to 10A (motor max 9.9A)
    - Lower temperature limit to 70°C (conservative for small motor)
    - Enable brake on stop for weapon safety
    - Reduce startup power to 5 (gentler on small motor)
    - Add hardware configuration analysis document
    Motor: FingerTech Silver Spark F2822-1100KV (0.125" shaft)
2025-11-18 docs: Add comprehensive hardware bringup plan
    Complete testing protocol for weapon motor system including:
    - ESC configuration with parameter adjuster
    - DShot protocol verification with oscilloscope
    - Motor characterization and thermal testing
    - EDT telemetry validation
    - Battery operation testing
2025-11-18 refactor: Comprehensive code cleanup and DShot enablement
    CRITICAL FIX: Enable DShot by default for weapon motor
    - Weapon now defaults to DShot300 mode (was PWM)
    - Hardware is configured for DShot on GP4
    - Provides faster response, digital protocol, and telemetry
    - Automatic fallback to PWM if DShot init fails
    Removed diagnostic mode (WiFi web server):
2026-01-29 docs: record DShot spin baseline
2026-01-29 test: add one-off DShot beep/spin tests
2026-01-30 Establish DShot/AM32 bench test baseline
2026-01-30 Improve EDT telemetry decode and add stats tool
2026-02-03 Improve DShot telemetry integration and test tooling
2026-02-03 Ignore local bench artifacts
2026-02-03 Add serial gamepad HITL input path
2026-02-03 Add serial HITL runner and telemetry commands
2026-02-06 Improve DShot telemetry handling and HITL tooling
2026-02-06 Add Pico W controller emulator skeleton
2026-02-06 Label HITL USB devices for easier identification
2026-02-06 Add HITL device setup docs and prefer stable tty aliases
2026-02-06 Enable picotool BOOTSEL reset for HITL Picos
2026-02-06 Add HITL orchestration framework
2026-02-06 Add weapon_spin HITL suite
2026-02-06 Make weapon_spin suite verify spin via PSU current
    - Add PSU current sampling + spin result artifacts to hitl_orchestrator
    - Raise default DShot update rate (500Hz) and switch weapon to unidirectional DShot for reliable spin
2026-02-07 hitl: add drive e2e suite and expose drive pulses
2026-02-07 hitl: fix e-stop PWM; avoid BT races; improve connect
2026-02-07 hitl: full e2e suite; fix gamepad right stick; hard stop on disconnect
2026-02-07 hitl: add drive spin suite; split drive/weapon PSU channels
2026-02-07 hitl: default drive PSU channel to CH1
2026-02-07 hitl: make drive stop-current check robust (tail median)
2026-02-07 hitl: generate md/pdf reports with plots; unify run artifacts
2026-02-07 hitl: validate left/right drive spin; tolerate PSU snapshot flakiness
2026-02-07 hitl: document system; add safety suites and invariants
2026-02-07 docs: expand HITL readme with diagrams
2026-02-08 docs: fix pin table in README
2026-02-08 competition: prevent startup drive lurch; fix weapon arming throttle
2026-02-08 safety: stop startup motor command; improve weapon input mapping
2026-02-08 hitl: add weapon latency suite and status markers
2026-02-09 hitl: fix BT sniff latency; improve weapon telemetry + latency test
2026-02-09 hitl: extend weapon latency drift test (axis sequence)
2026-02-09 competition: fix weapon stick range dropouts
